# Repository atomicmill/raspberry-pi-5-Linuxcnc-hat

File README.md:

Raspberry Pi 5 Linuxcnc hat KiCad proect

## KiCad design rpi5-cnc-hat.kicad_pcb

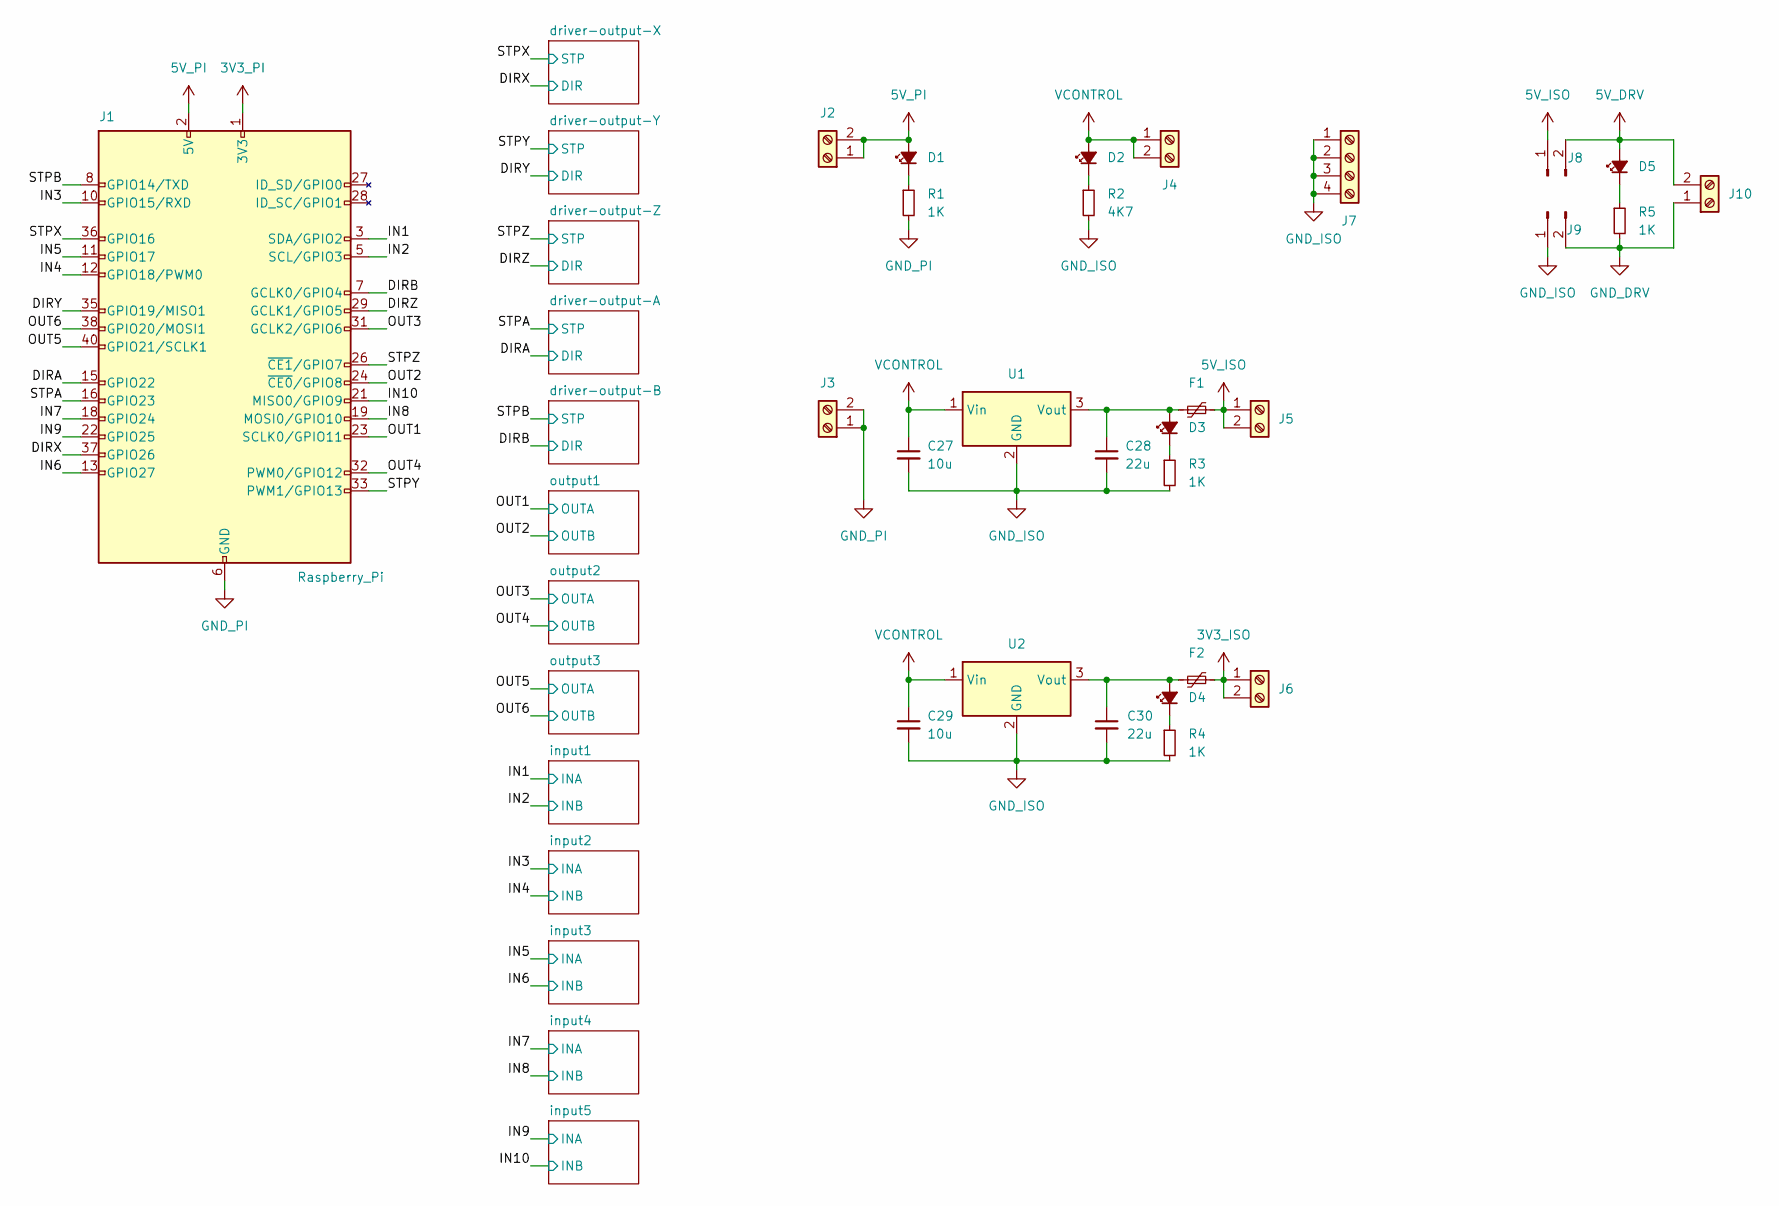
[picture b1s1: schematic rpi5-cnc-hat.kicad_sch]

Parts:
C27, C29: 10u; C_0805_2012Metric_Pad1.18x1.45mm_HandSolder
C28, C30: 22u; C_0805_2012Metric_Pad1.18x1.45mm_HandSolder
D1, D2, D3, D4, D5: LED_Small_Filled; LED_0805_2012Metric_Pad1.15x1.40mm_HandSolder
F1, F2: Polyfuse_Small; Fuse_1206_3216Metric_Pad1.42x1.75mm_HandSolder
J1: Raspberry_Pi; raspberrypi
J2, J3, J4, J5, J6, J10: Screw_Terminal_01x02; TerminalBlock_Phoenix_PT-1,5-2-3.5-H_1x02_P3.50mm_Horizontal
J7: Screw_Terminal_01x04; TerminalBlock_Phoenix_PT-1,5-4-3.5-H_1x04_P3.50mm_Horizontal
J8, J9: Conn_01x02_Pin; PinHeader_1x02_P2.54mm_Vertical
R1, R3, R4, R5: 1K; R_0805_2012Metric_Pad1.20x1.40mm_HandSolder
R2: 4K7; R_0805_2012Metric_Pad1.20x1.40mm_HandSolder
U1: TSR_1-2450; Converter_DCDC_TRACO_TSR-1_THT
U2: TSR_1-2433; Converter_DCDC_TRACO_TSR-1_THT

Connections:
3V3_ISO: F2.2, J6.1, J6.2
3V3_PI: J1.1 (3V3), J1.17 (3V3); also elsewhere on the board
5V_DRV: D5.2 (A), J8.2, J10.2; also elsewhere on the board
5V_ISO: F1.2, J5.1, J5.2, J8.1; also elsewhere on the board
5V_PI: D1.2 (A), J1.2 (5V), J1.4 (5V), J2.1, J2.2
/DIRA: J1.15 (GPIO22); also elsewhere on the board
/DIRB: J1.7 (GCLK0/GPIO4); also elsewhere on the board
/DIRX: J1.37 (GPIO26); also elsewhere on the board
/DIRY: J1.35 (GPIO19/MISO1); also elsewhere on the board
/DIRZ: J1.29 (GCLK1/GPIO5); also elsewhere on the board
/IN1: J1.3 (SDA/GPIO2); also elsewhere on the board
/IN2: J1.5 (SCL/GPIO3); also elsewhere on the board
/IN3: J1.10 (GPIO15/RXD); also elsewhere on the board
/IN4: J1.12 (GPIO18/PWM0); also elsewhere on the board
/IN5: J1.11 (GPIO17); also elsewhere on the board
/IN6: J1.13 (GPIO27); also elsewhere on the board
/IN7: J1.18 (GPIO24); also elsewhere on the board
/IN8: J1.19 (MOSI0/GPIO10); also elsewhere on the board
/IN9: J1.22 (GPIO25); also elsewhere on the board
/IN10: J1.21 (MISO0/GPIO9); also elsewhere on the board
/OUT1: J1.23 (SCLK0/GPIO11); also elsewhere on the board
/OUT2: J1.24 (~CE0/GPIO8); also elsewhere on the board
/OUT3: J1.31 (GCLK2/GPIO6); also elsewhere on the board
/OUT4: J1.32 (PWM0/GPIO12); also elsewhere on the board
/OUT5: J1.40 (GPIO21/SCLK1); also elsewhere on the board
/OUT6: J1.38 (GPIO20/MOSI1); also elsewhere on the board
/STPA: J1.16 (GPIO23); also elsewhere on the board
/STPB: J1.8 (GPIO14/TXD); also elsewhere on the board
/STPX: J1.36 (GPIO16); also elsewhere on the board
/STPY: J1.33 (PWM1/GPIO13); also elsewhere on the board
/STPZ: J1.26 (~CE1/GPIO7); also elsewhere on the board
GND_DRV: J9.2, J10.1, R5.2; also elsewhere on the board
GND_ISO: C27.2, C28.2, C29.2, C30.2, J7.1, J7.2, J7.3, J7.4, J9.1, R2.2, R3.2, R4.2, U1.2 (GND), U2.2 (GND); also elsewhere on the board
GND_PI: J1.6 (GND), J1.9 (GND), J1.14 (GND), J1.20 (GND), J1.25 (GND), J1.30 (GND), J1.34 (GND), J1.39 (GND), J3.1, J3.2, R1.2; also elsewhere on the board
unnamed: D1.1 (K), R1.1
unnamed: D2.1 (K), R2.1
unnamed: C28.1, D3.2 (A), F1.1, U1.3 (Vout)
unnamed: D3.1 (K), R3.1
unnamed: C30.1, D4.2 (A), F2.1, U2.3 (Vout)
unnamed: D4.1 (K), R4.1
unnamed: D5.1 (K), R5.1
VCONTROL: C27.1, C29.1, D2.2 (A), J4.1, J4.2, U1.1 (Vin), U2.1 (Vin)

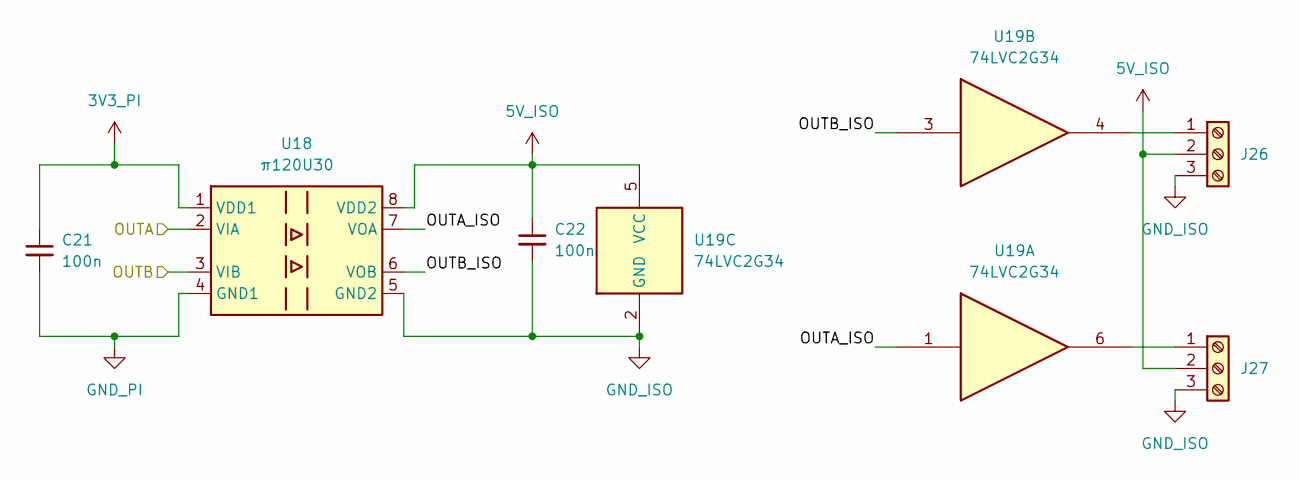
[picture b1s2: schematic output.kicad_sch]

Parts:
C21, C22: 100n; C_0805_2012Metric_Pad1.18x1.45mm_HandSolder
J26, J27: Screw_Terminal_01x03; TerminalBlock_Phoenix_PT-1,5-3-3.5-H_1x03_P3.50mm_Horizontal
U18: π120U30; SOIC-8_3.9x4.9mm_P1.27mm
U19: 74LVC2G34; SOT-23-6_Handsoldering

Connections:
3V3_PI: C21.1, U18.1 (VDD1); also elsewhere on the board
5V_ISO: C22.1, J26.2, J27.2, U18.8 (VDD2), U19.5 (VCC); also elsewhere on the board
/OUT1: U18.2 (VIA); also elsewhere on the board
/OUT2: U18.3 (VIB); also elsewhere on the board
/output1/OUTA_ISO: U18.7 (VOA), U19.1
/output1/OUTB_ISO: U18.6 (VOB), U19.3
GND_ISO: C22.2, J26.3, J27.3, U18.5 (GND2), U19.2 (GND); also elsewhere on the board
GND_PI: C21.2, U18.4 (GND1); also elsewhere on the board
unnamed: J26.1, U19.4
unnamed: J27.1, U19.6

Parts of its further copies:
C23, C24, C25, C26: 100n; C_0805_2012Metric_Pad1.18x1.45mm_HandSolder
J28, J29, J30, J31: Screw_Terminal_01x03; TerminalBlock_Phoenix_PT-1,5-3-3.5-H_1x03_P3.50mm_Horizontal
U20, U22: π120U30; SOIC-8_3.9x4.9mm_P1.27mm
U21, U23: 74LVC2G34; SOT-23-6_Handsoldering

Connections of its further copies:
3V3_PI: C23.1, C25.1, U20.1 (VDD1), U22.1 (VDD1); also elsewhere on the board
5V_ISO: C24.1, C26.1, J28.2, J29.2, J30.2, J31.2, U20.8 (VDD2), U21.5 (VCC), U22.8 (VDD2), U23.5 (VCC); also elsewhere on the board
/OUT3: U20.2 (VIA); also elsewhere on the board
/OUT4: U20.3 (VIB); also elsewhere on the board
/OUT5: U22.2 (VIA); also elsewhere on the board
/OUT6: U22.3 (VIB); also elsewhere on the board
/output2/OUTA_ISO: U20.7 (VOA), U21.1
/output2/OUTB_ISO: U20.6 (VOB), U21.3
/output3/OUTA_ISO: U22.7 (VOA), U23.1
/output3/OUTB_ISO: U22.6 (VOB), U23.3
GND_ISO: C24.2, C26.2, J28.3, J29.3, J30.3, J31.3, U20.5 (GND2), U21.2 (GND), U22.5 (GND2), U23.2 (GND); also elsewhere on the board
GND_PI: C23.2, C25.2, U20.4 (GND1), U22.4 (GND1); also elsewhere on the board
unnamed: J28.1, U21.4
unnamed: J29.1, U21.6
unnamed: J30.1, U23.4
unnamed: J31.1, U23.6

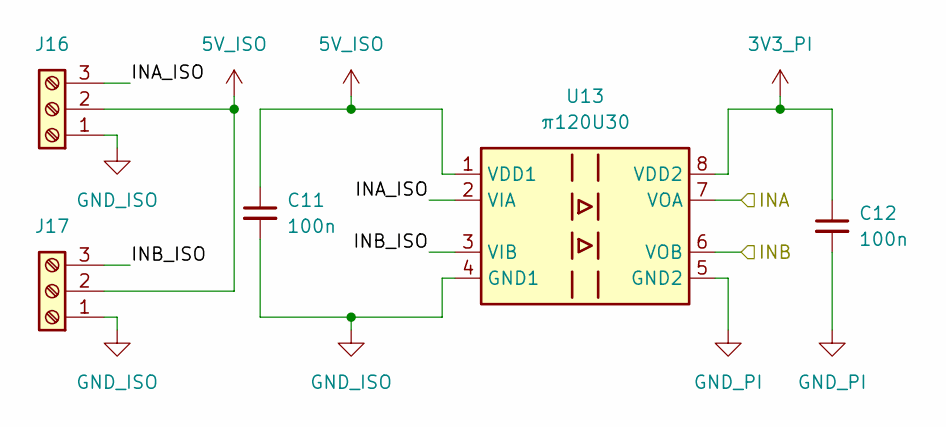
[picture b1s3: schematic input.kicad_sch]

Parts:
C11, C12: 100n; C_0805_2012Metric_Pad1.18x1.45mm_HandSolder
J16, J17: Screw_Terminal_01x03; TerminalBlock_Phoenix_PT-1,5-3-3.5-H_1x03_P3.50mm_Horizontal
U13: π120U30; SOIC-8_3.9x4.9mm_P1.27mm

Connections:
3V3_PI: C12.1, U13.8 (VDD2); also elsewhere on the board
5V_ISO: C11.1, J16.2, J17.2, U13.1 (VDD1); also elsewhere on the board
/IN1: U13.7 (VOA); also elsewhere on the board
/IN2: U13.6 (VOB); also elsewhere on the board
/input1/INA_ISO: J16.3, U13.2 (VIA)
/input1/INB_ISO: J17.3, U13.3 (VIB)
GND_ISO: C11.2, J16.1, J17.1, U13.4 (GND1); also elsewhere on the board
GND_PI: C12.2, U13.5 (GND2); also elsewhere on the board

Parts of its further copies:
C13, C14, C15, C16, C17, C18, C19, C20: 100n; C_0805_2012Metric_Pad1.18x1.45mm_HandSolder
J18, J19, J20, J21, J22, J23, J24, J25: Screw_Terminal_01x03; TerminalBlock_Phoenix_PT-1,5-3-3.5-H_1x03_P3.50mm_Horizontal
U14, U15, U16, U17: π120U30; SOIC-8_3.9x4.9mm_P1.27mm

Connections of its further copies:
3V3_PI: C14.1, C16.1, C18.1, C20.1, U14.8 (VDD2), U15.8 (VDD2), U16.8 (VDD2), U17.8 (VDD2); also elsewhere on the board
5V_ISO: C13.1, C15.1, C17.1, C19.1, J18.2, J19.2, J20.2, J21.2, J22.2, J23.2, J24.2, J25.2, U14.1 (VDD1), U15.1 (VDD1), U16.1 (VDD1), U17.1 (VDD1); also elsewhere on the board
/IN3: U14.7 (VOA); also elsewhere on the board
/IN4: U14.6 (VOB); also elsewhere on the board
/IN5: U15.7 (VOA); also elsewhere on the board
/IN6: U15.6 (VOB); also elsewhere on the board
/IN7: U16.7 (VOA); also elsewhere on the board
/IN8: U16.6 (VOB); also elsewhere on the board
/IN9: U17.7 (VOA); also elsewhere on the board
/IN10: U17.6 (VOB); also elsewhere on the board
/input2/INA_ISO: J18.3, U14.2 (VIA)
/input2/INB_ISO: J19.3, U14.3 (VIB)
/input3/INA_ISO: J20.3, U15.2 (VIA)
/input3/INB_ISO: J21.3, U15.3 (VIB)
/input4/INA_ISO: J22.3, U16.2 (VIA)
/input4/INB_ISO: J23.3, U16.3 (VIB)
/input5/INA_ISO: J24.3, U17.2 (VIA)
/input5/INB_ISO: J25.3, U17.3 (VIB)
GND_ISO: C13.2, C15.2, C17.2, C19.2, J18.1, J19.1, J20.1, J21.1, J22.1, J23.1, J24.1, J25.1, U14.4 (GND1), U15.4 (GND1), U16.4 (GND1), U17.4 (GND1); also elsewhere on the board
GND_PI: C14.2, C16.2, C18.2, C20.2, U14.5 (GND2), U15.5 (GND2), U16.5 (GND2), U17.5 (GND2); also elsewhere on the board

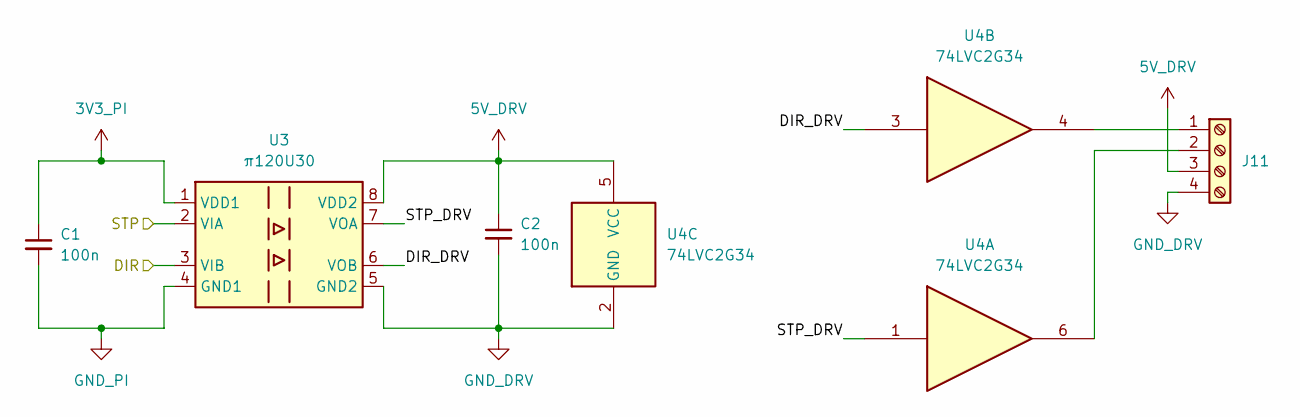
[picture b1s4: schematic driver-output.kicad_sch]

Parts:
C1, C2: 100n; C_0805_2012Metric_Pad1.18x1.45mm_HandSolder
J11: Screw_Terminal_01x04; TerminalBlock_Phoenix_PT-1,5-4-3.5-H_1x04_P3.50mm_Horizontal
U3: π120U30; SOIC-8_3.9x4.9mm_P1.27mm
U4: 74LVC2G34; SOT-23-6_Handsoldering

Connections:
3V3_PI: C1.1, U3.1 (VDD1); also elsewhere on the board
5V_DRV: C2.1, J11.3, U3.8 (VDD2), U4.5 (VCC); also elsewhere on the board
/DIRX: U3.3 (VIB); also elsewhere on the board
/STPX: U3.2 (VIA); also elsewhere on the board
/driver-output-X/DIR_DRV: U3.6 (VOB), U4.3
/driver-output-X/STP_DRV: U3.7 (VOA), U4.1
GND_DRV: C2.2, J11.4, U3.5 (GND2), U4.2 (GND); also elsewhere on the board
GND_PI: C1.2, U3.4 (GND1); also elsewhere on the board
unnamed: J11.1, U4.4
unnamed: J11.2, U4.6

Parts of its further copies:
C3, C4, C5, C6, C7, C8, C9, C10: 100n; C_0805_2012Metric_Pad1.18x1.45mm_HandSolder
J12, J13, J14, J15: Screw_Terminal_01x04; TerminalBlock_Phoenix_PT-1,5-4-3.5-H_1x04_P3.50mm_Horizontal
U5, U7, U9, U11: π120U30; SOIC-8_3.9x4.9mm_P1.27mm
U6, U8, U10, U12: 74LVC2G34; SOT-23-6_Handsoldering

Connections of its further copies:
3V3_PI: C3.1, C5.1, C7.1, C9.1, U5.1 (VDD1), U7.1 (VDD1), U9.1 (VDD1), U11.1 (VDD1); also elsewhere on the board
5V_DRV: C4.1, C6.1, C8.1, C10.1, J12.3, J13.3, J14.3, J15.3, U5.8 (VDD2), U6.5 (VCC), U7.8 (VDD2), U8.5 (VCC), U9.8 (VDD2), U10.5 (VCC), U11.8 (VDD2), U12.5 (VCC); also elsewhere on the board
/DIRA: U9.3 (VIB); also elsewhere on the board
/DIRB: U11.3 (VIB); also elsewhere on the board
/DIRY: U5.3 (VIB); also elsewhere on the board
/DIRZ: U7.3 (VIB); also elsewhere on the board
/STPA: U9.2 (VIA); also elsewhere on the board
/STPB: U11.2 (VIA); also elsewhere on the board
/STPY: U5.2 (VIA); also elsewhere on the board
/STPZ: U7.2 (VIA); also elsewhere on the board
/driver-output-A/DIR_DRV: U9.6 (VOB), U10.3
/driver-output-A/STP_DRV: U9.7 (VOA), U10.1
/driver-output-B/DIR_DRV: U11.6 (VOB), U12.3
/driver-output-B/STP_DRV: U11.7 (VOA), U12.1
/driver-output-Y/DIR_DRV: U5.6 (VOB), U6.3
/driver-output-Y/STP_DRV: U5.7 (VOA), U6.1
/driver-output-Z/DIR_DRV: U7.6 (VOB), U8.3
/driver-output-Z/STP_DRV: U7.7 (VOA), U8.1
GND_DRV: C4.2, C6.2, C8.2, C10.2, J12.4, J13.4, J14.4, J15.4, U5.5 (GND2), U6.2 (GND), U7.5 (GND2), U8.2 (GND), U9.5 (GND2), U10.2 (GND), U11.5 (GND2), U12.2 (GND); also elsewhere on the board
GND_PI: C3.2, C5.2, C7.2, C9.2, U5.4 (GND1), U7.4 (GND1), U9.4 (GND1), U11.4 (GND1); also elsewhere on the board
unnamed: J12.1, U6.4
unnamed: J12.2, U6.6
unnamed: J13.1, U8.4
unnamed: J13.2, U8.6
unnamed: J14.1, U10.4
unnamed: J14.2, U10.6
unnamed: J15.1, U12.4
unnamed: J15.2, U12.6

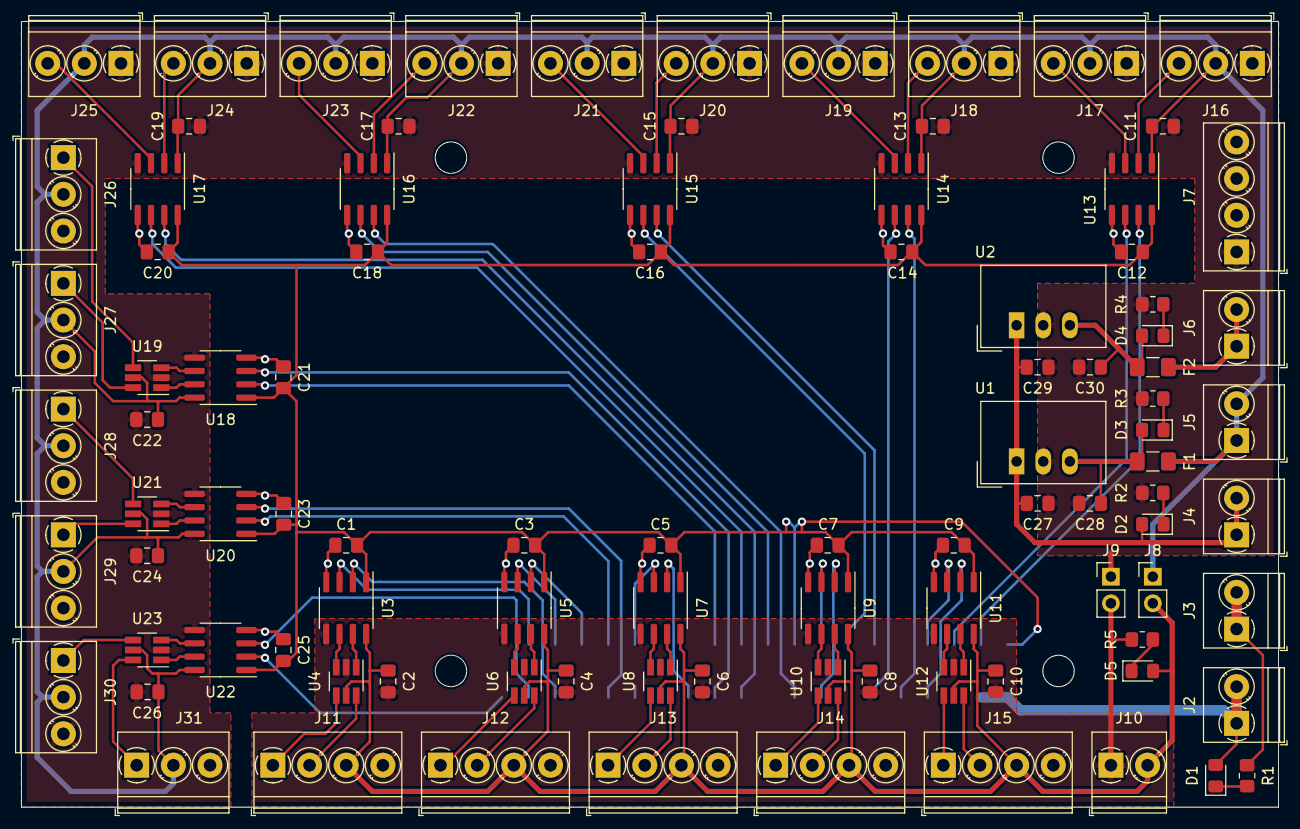
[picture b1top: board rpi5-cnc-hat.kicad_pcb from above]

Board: 2 copper layers, 120.0 x 75.0 mm, 96 parts (1 on the bottom side), 84 nets.

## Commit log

2024-08-22 created project repo
2024-08-22 photo
